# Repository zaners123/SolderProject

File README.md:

# SolderProject
A Project to teach Students how to Solder

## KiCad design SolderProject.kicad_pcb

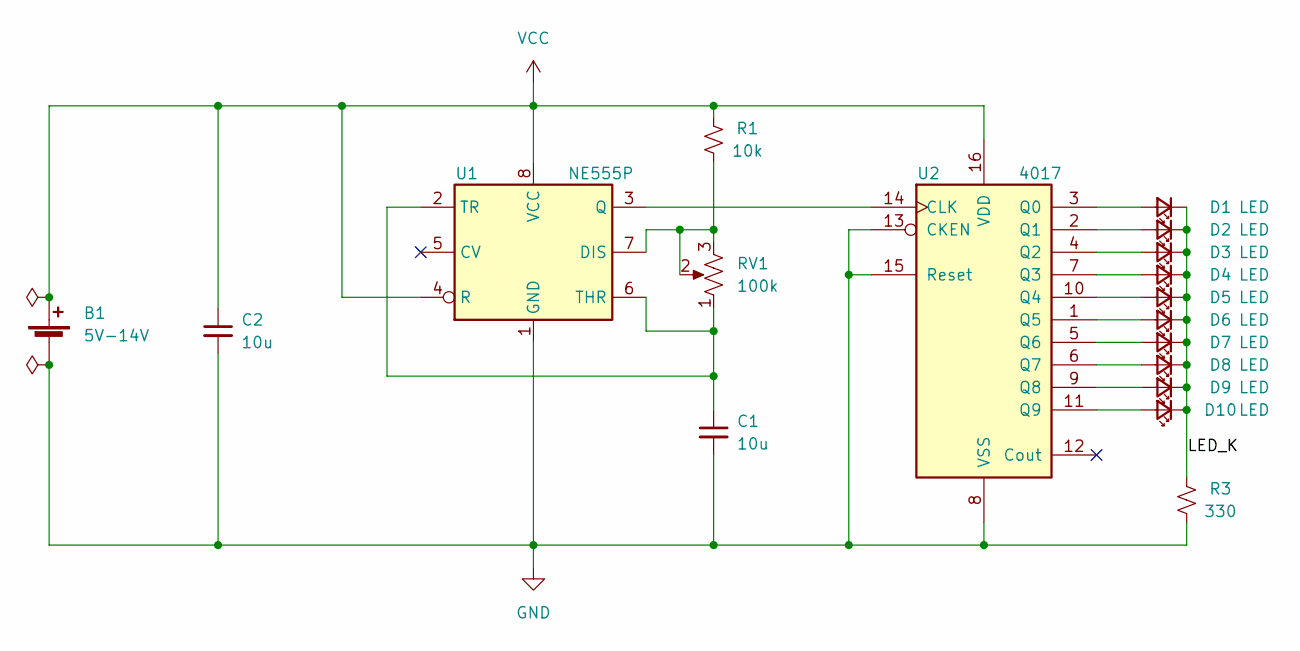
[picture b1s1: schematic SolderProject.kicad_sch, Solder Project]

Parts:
B1: 5V-14V; PinHeader_1x02_P2.54mm_Vertical
C1, C2: 10u; CP_Radial_D5.0mm_P2.00mm
D1, D2, D3, D4, D5, D6, D7, D8, D9, D10: LED; LED_D4.0mm
R1: 10k; R_Axial_DIN0207_L6.3mm_D2.5mm_P10.16mm_Horizontal
R3: 330; R_Axial_DIN0207_L6.3mm_D2.5mm_P10.16mm_Horizontal
RV1: 100k; trimpot-3306KPW
U1: NE555P; DIP-8_W7.62mm
U2: 4017; DIP-16_W7.62mm

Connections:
/LED_K: D1.1 (K), D2.1 (K), D3.1 (K), D4.1 (K), D5.1 (K), D6.1 (K), D7.1 (K), D8.1 (K), D9.1 (K), D10.1 (K), R3.1
GND: B1.2 (-), C1.2, C2.2, R3.2, U1.1 (GND), U2.8 (VSS), U2.13 (CKEN), U2.15 (Reset)
unnamed: C1.1, RV1.1, U1.2 (TR), U1.6 (THR)
unnamed: D1.2 (A), U2.3 (Q0)
unnamed: D2.2 (A), U2.2 (Q1)
unnamed: D3.2 (A), U2.4 (Q2)
unnamed: D4.2 (A), U2.7 (Q3)
unnamed: D5.2 (A), U2.10 (Q4)
unnamed: D6.2 (A), U2.1 (Q5)
unnamed: D7.2 (A), U2.5 (Q6)
unnamed: D8.2 (A), U2.6 (Q7)
unnamed: D9.2 (A), U2.9 (Q8)
unnamed: D10.2 (A), U2.11 (Q9)
unnamed: R1.1, RV1.2, RV1.3, U1.7 (DIS)
unnamed: U1.3 (Q), U2.14 (CLK)
VCC: B1.1 (+), C2.1, R1.2, U1.4 (R), U1.8 (VCC), U2.16 (VDD)

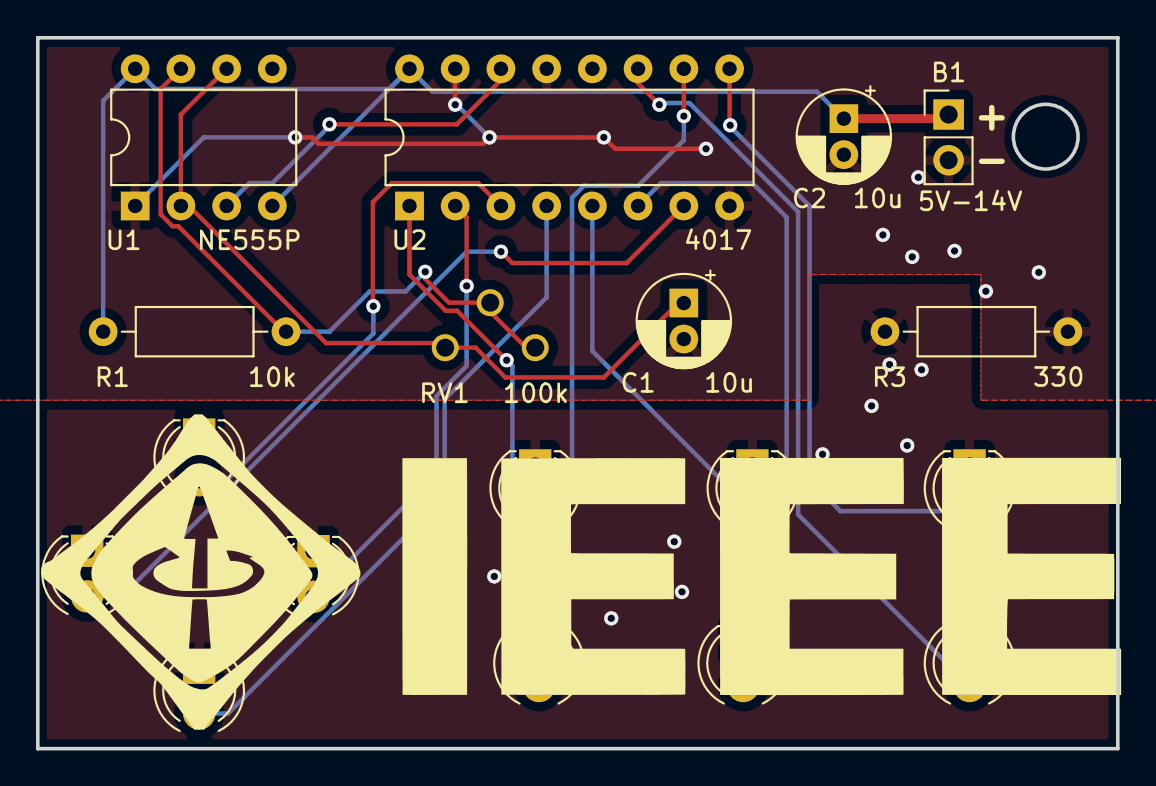
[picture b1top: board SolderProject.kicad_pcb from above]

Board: 2 copper layers, 60.0 x 39.5 mm, 18 parts (0 on the bottom side), 16 nets.

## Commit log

2023-03-02 V1.1 - Slight improvements VMax changed to 14V
